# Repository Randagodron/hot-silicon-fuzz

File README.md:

# Hot Silicon Fuzz
Re-implementation of the FoxRox Hot Silicon Fuzz.

Full analog fuzz with bias and tone control, silicon transistors, relay true bypass, 1590A enclosure format.

Simulated with LTSpice, designed with Kicad. All simulations and CAD files are provided under creative commons CC-BY-SA 4.0

Companion article (in french) : http://blog.randagodron.eu/index.php?post/2018/02/04/DIY-audio-Hot-Silicon-Fuzz

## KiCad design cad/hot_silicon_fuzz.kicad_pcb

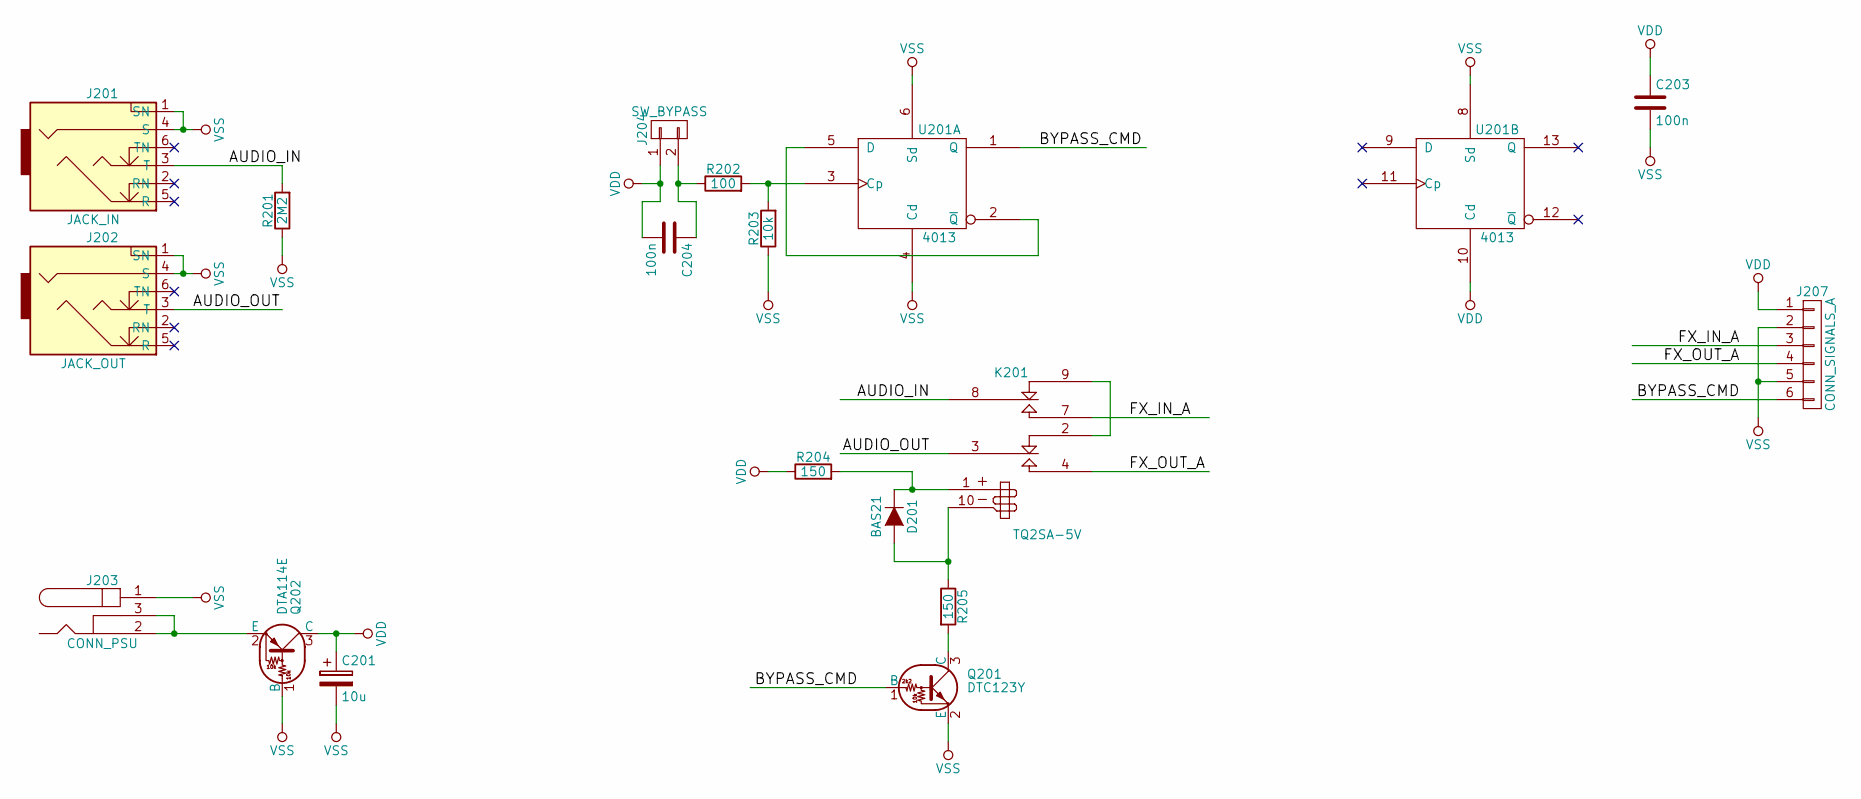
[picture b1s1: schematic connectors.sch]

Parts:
C201: 10u; CP_Elec_4x4.5
C203, C204: 100n; C_0603
D201: BAS21; SOT-23
J201: JACK_IN; CLIFF_FCR5005x
J202: JACK_OUT; CLIFF_FCR5005x
J203: CONN_PSU; JACK_ALIM
J204: SW_BYPASS; Pin_Header_Straight_1x02_Pitch2.54mm
J207: CONN_SIGNALS_A; Pin_Header_Straight_1x06_Pitch2.54mm
K201: TQ2SA-5V; TQ2SA
Q201: DTC123Y; SOT-23
Q202: DTA114E; SOT-23
R201: 2M2; R_0603
R202: 100; R_0603
R203: 10k; R_0603
R204, R205: 150; R_0805
U201: 4013; SOIC-14_N

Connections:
/CONNECTORS/AUDIO_IN: J201.3 (T), K201.8 (C2), R201.2
/CONNECTORS/AUDIO_OUT: J202.3 (T), K201.3 (C1)
/CONNECTORS/BYPASS_CMD: J207.6, Q201.1 (B), U201.1 (Q)
/CONNECTORS/FX_IN_A: J207.3, K201.7 (T2)
/CONNECTORS/FX_OUT_A: J207.4, K201.4 (T1)
unnamed: C204.1, J204.2, R202.1
unnamed: D201.1 (A), K201.10 (-), R205.1
unnamed: D201.3 (K), K201.1 (+), R204.2
unnamed: J203.2, J203.3, Q202.2 (E)
unnamed: K201.2 (R1), K201.9 (R2)
unnamed: Q201.3 (C), R205.2
unnamed: R202.2, R203.2, U201.3 (Cp)
unnamed: U201.2 (~Q), U201.5 (D)
VDD: C201.1, C203.1, C204.2, J204.1, J207.1, Q202.3 (C), R204.1, U201.10 (Cd), U201.14 (VDD)
VSS: C201.2, C203.2, J201.1 (SN), J201.4 (S), J202.1 (SN), J202.4 (S), J203.1, J207.2, J207.5, Q201.2 (E), Q202.1 (B), R201.1, R203.1, U201.4 (Cd), U201.6 (Sd), U201.7 (VSS), U201.8 (Sd)

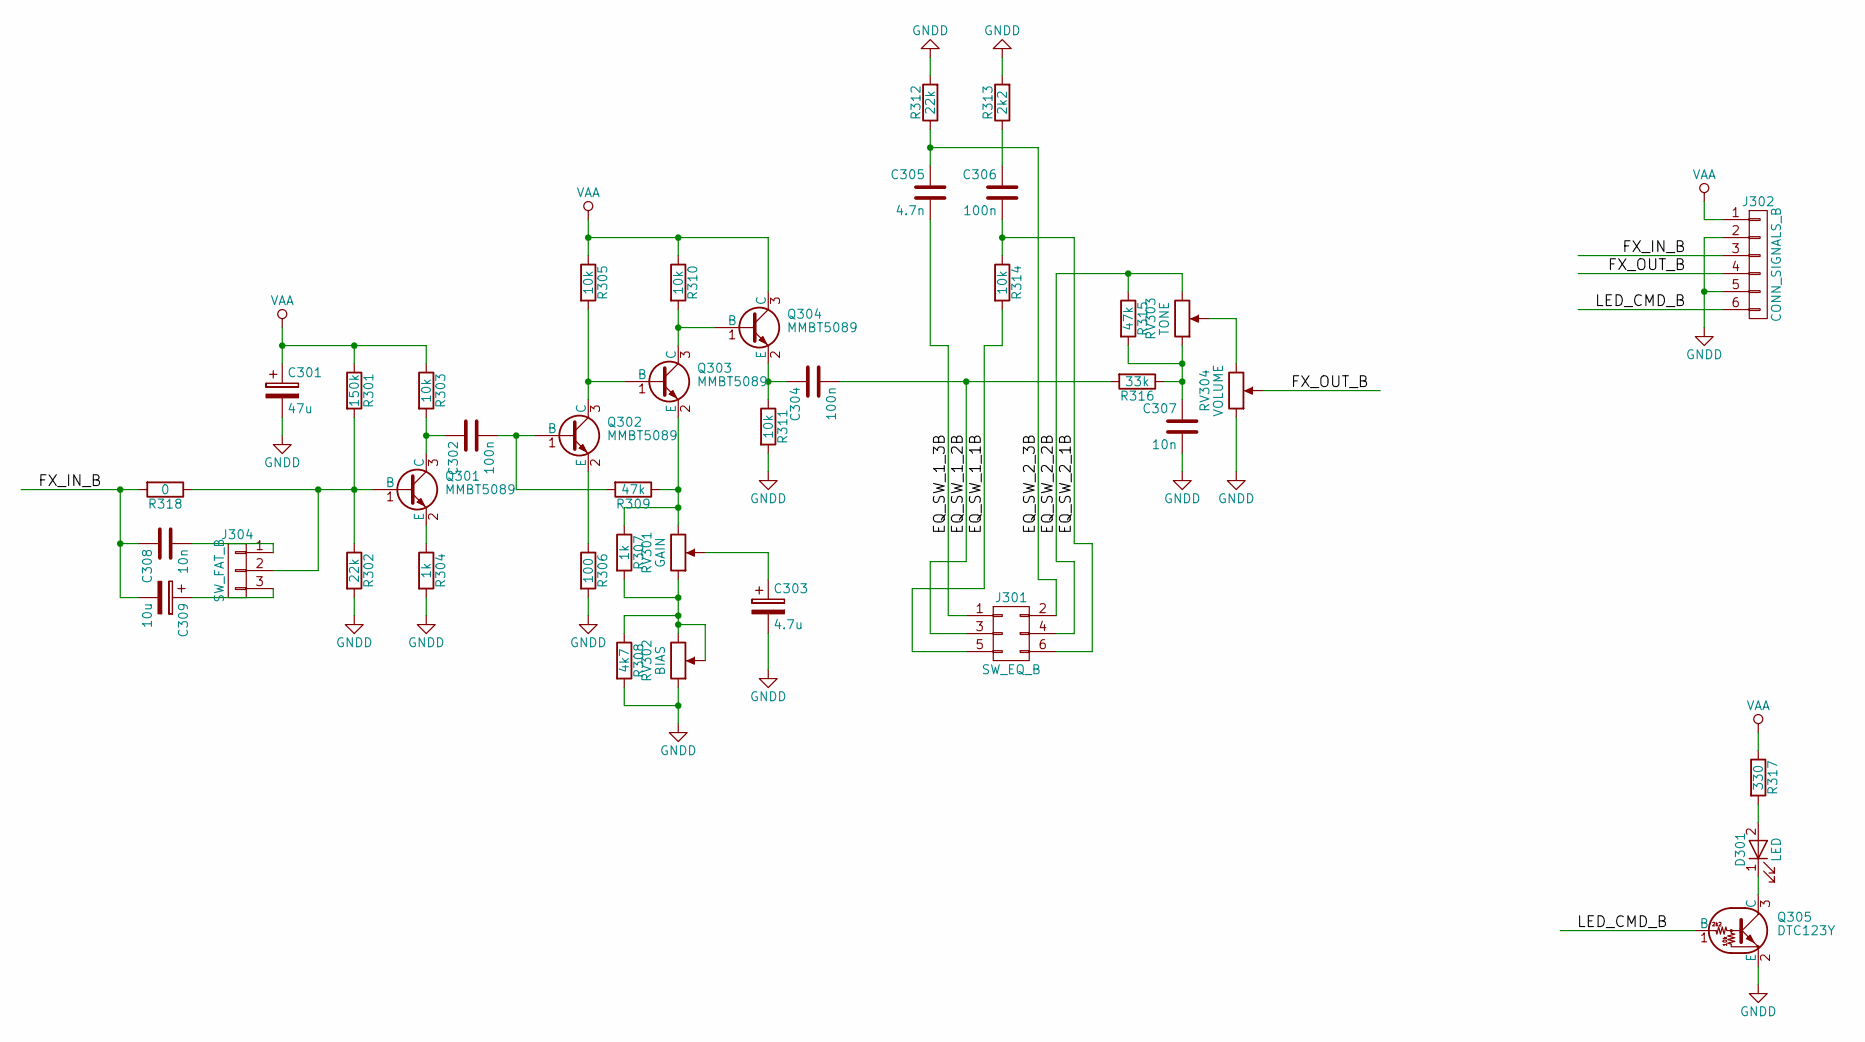
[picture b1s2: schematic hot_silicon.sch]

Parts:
C301: 47u; CP_Elec_5x5.3
C302, C304, C306: 100n; C_0603
C303: 4.7u; CP_Elec_5x5.3
C305: 4.7n; C_0603
C307, C308: 10n; C_0603
C309: 10u; CP_Elec_5x5.3
D301: LED; Pin_Header_Straight_1x02_Pitch2.54mm
J301: SW_EQ_B; Multicomp_sub-miniature_DPDT
J302: CONN_SIGNALS_B; Pin_Header_Straight_1x06_Pitch2.54mm
J304: SW_FAT_B; Pin_Header_Straight_1x03_Pitch2.54mm
Q301, Q302, Q303, Q304: MMBT5089; SOT-23
Q305: DTC123Y; SOT-23
R301: 150k; R_0603
R302, R312: 22k; R_0603
R303, R305, R310, R311, R314: 10k; R_0603
R304, R307: 1k; R_0603
R306: 100; R_0603
R308: 4k7; R_0603
R309, R315: 47k; R_0603
R313: 2k2; R_0603
R316: 33k; R_0603
R317: 330; R_0805
R318: 0; R_0603
RV301: GAIN; ALPS_RK09L
RV302: BIAS; ALPS_RK09L
RV303: TONE; ALPS_RK09L
RV304: VOLUME; ALPS_RK09L

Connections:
/Hot Silicon/EQ_SW_1_1B: J301.5, R314.2
/Hot Silicon/EQ_SW_1_2B: C304.2, J301.3, R316.2
/Hot Silicon/EQ_SW_1_3B: C305.2, J301.1
/Hot Silicon/EQ_SW_2_1B: C306.2, J301.6, R314.1
/Hot Silicon/EQ_SW_2_2B: J301.4, R315.1, RV303.3
/Hot Silicon/EQ_SW_2_3B: C305.1, J301.2, R312.1
/Hot Silicon/FX_IN_B: C308.1, C309.2, J302.3, R318.2
/Hot Silicon/FX_OUT_B: J302.4, RV304.2
/Hot Silicon/LED_CMD_B: J302.6, Q305.1 (B)
GNDD: C301.2, C303.2, C307.2, J302.2, J302.5, Q305.2 (E), R302.2, R304.2, R306.2, R308.2, R311.2, R312.2, R313.2, RV302.1, RV304.1
unnamed: C302.1, Q301.3 (C), R303.2
unnamed: C302.2, Q302.1 (B), R309.2
unnamed: C303.1, RV301.2
unnamed: C304.1, Q304.2 (E), R311.1
unnamed: C306.1, R313.1
unnamed: C307.1, R315.2, R316.1, RV303.1
unnamed: C308.2, J304.1
unnamed: C309.1, J304.3
unnamed: D301.1 (K), Q305.3 (C)
unnamed: D301.2 (A), R317.2
unnamed: J304.2, Q301.1 (B), R301.2, R302.1, R318.1
unnamed: Q301.2 (E), R304.1
unnamed: Q302.2 (E), R306.1
unnamed: Q302.3 (C), Q303.1 (B), R305.2
unnamed: Q303.2 (E), R307.1, R309.1, RV301.3
unnamed: Q303.3 (C), Q304.1 (B), R310.2
unnamed: R307.2, R308.1, RV301.1, RV302.2, RV302.3
unnamed: RV303.2, RV304.3
VAA: C301.1, J302.1, Q304.3 (C), R301.1, R303.1, R305.1, R310.1, R317.1

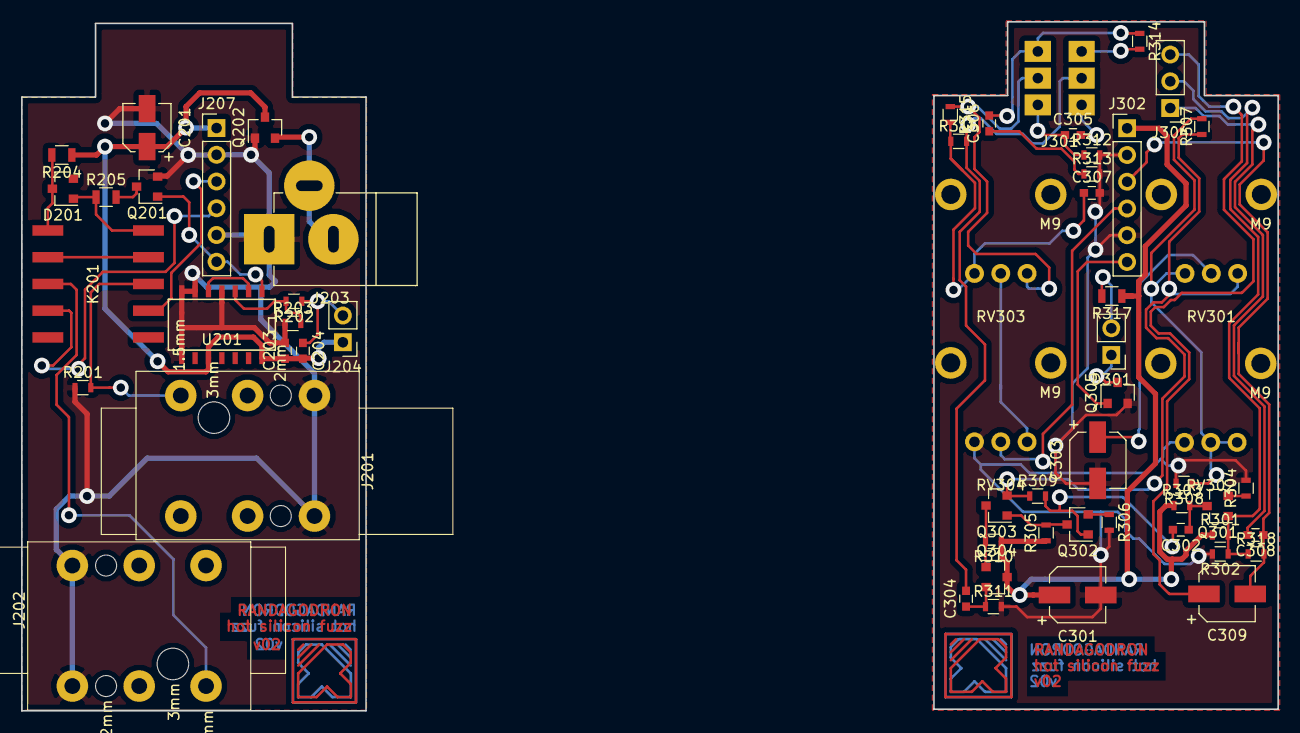
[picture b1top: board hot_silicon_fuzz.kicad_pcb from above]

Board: 2 copper layers, 119.3 x 65.4 mm, 58 parts (0 on the bottom side), 44 nets.

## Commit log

2017-08-28 First commit.
    Schematic done.
2017-08-28 Placed components. Added possibility of having switches on connector board or circuit board.
2017-09-01 Corrected pots orientation.
    Finished layout.
2017-12-09 Exported layout.
    Done simulations.
2017-12-09 Corrections on layout.
    Exported layout.
2017-12-29 Corrected layout
2018-02-04 Added recorded samples of the pedal.
2018-08-15 Added signals plots and exported samples.
2018-12-06 Added fiducials.
    Re-exported layout.
